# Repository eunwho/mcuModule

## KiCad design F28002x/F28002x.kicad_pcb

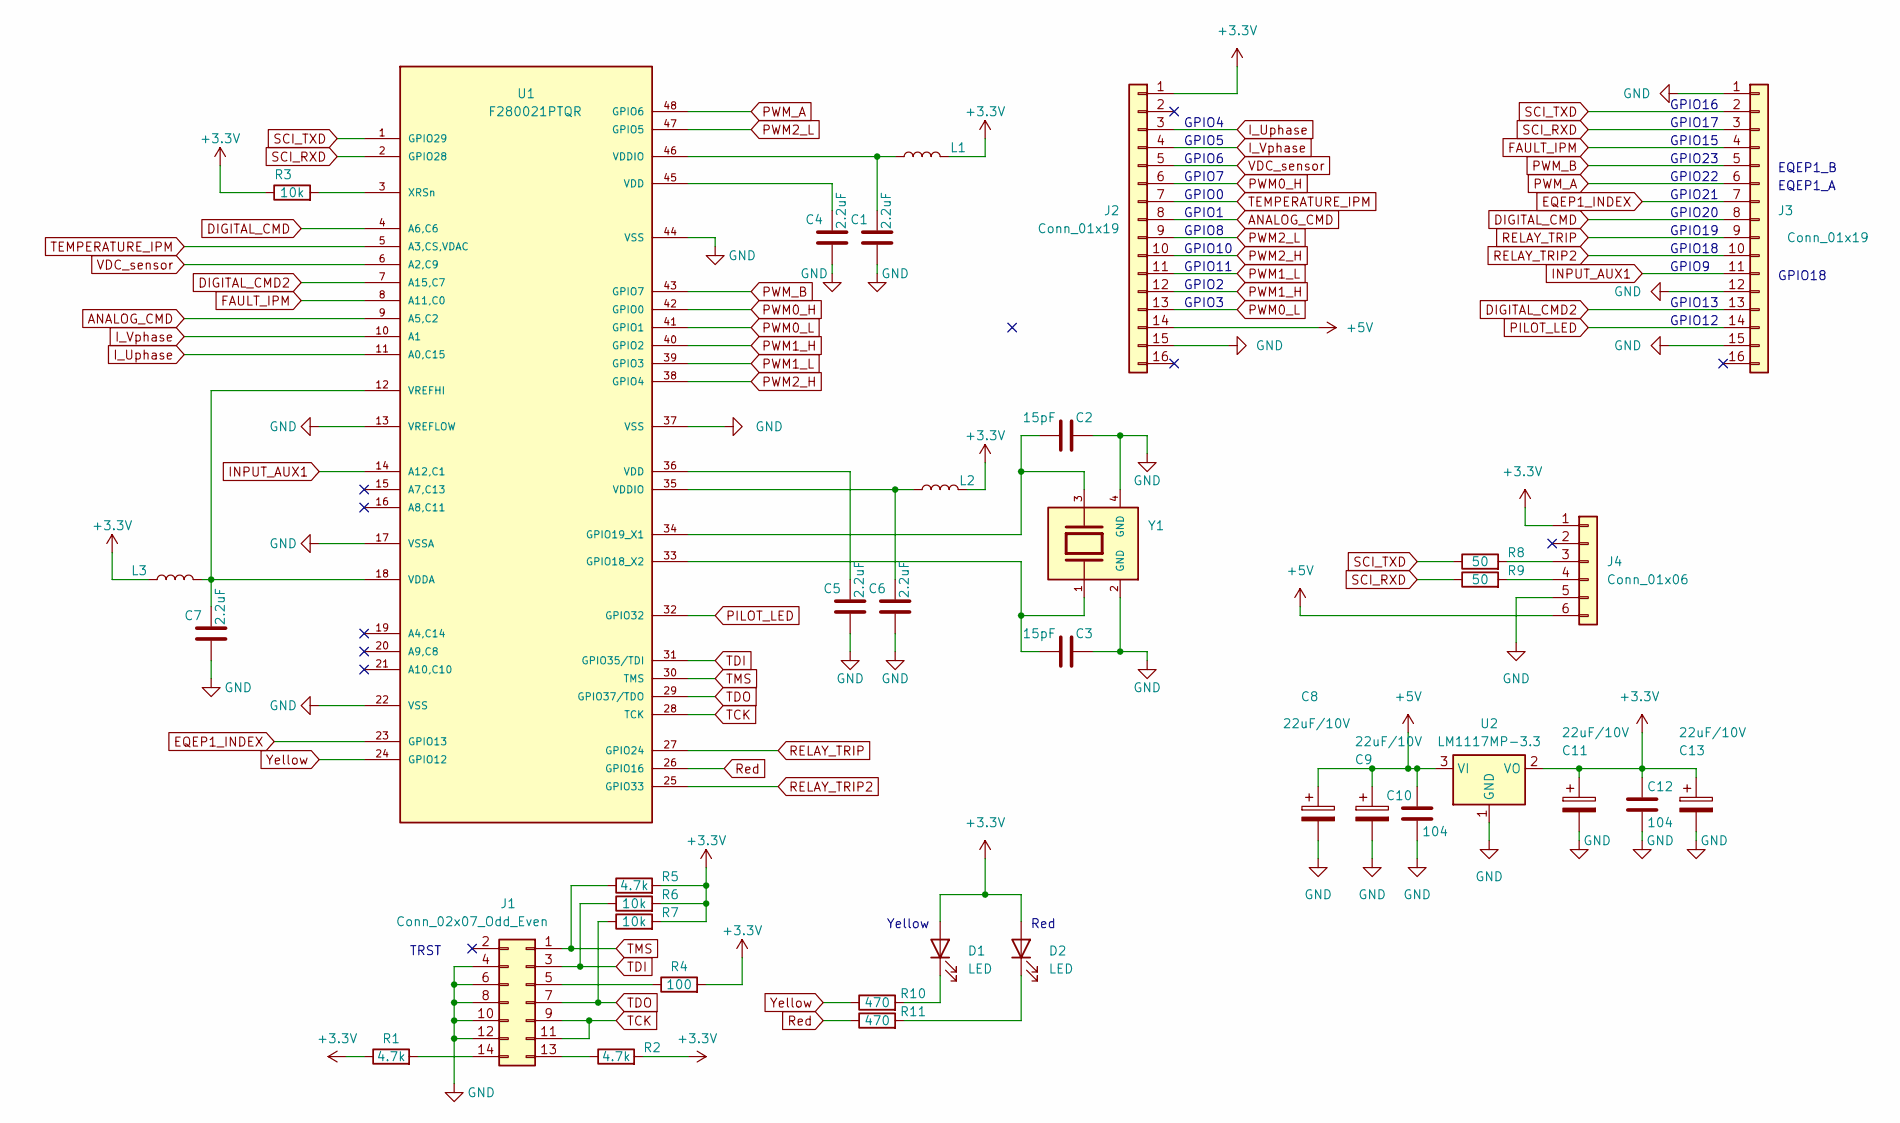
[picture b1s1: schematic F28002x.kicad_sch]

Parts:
C1, C4, C5, C6, C7: 2.2uF; C_0805_2012Metric
C2, C3: 15pF; C_0805_2012Metric
C8, C9, C11, C13: 22uF/10V; C_1210_3225Metric_Pad1.33x2.70mm_HandSolder
C10, C12: 104; C_0805_2012Metric
D1, D2: LED; LED_0805_2012Metric_Pad1.15x1.40mm_HandSolder
J1: Conn_02x07_Odd_Even; PinHeader_2x07_P2.54mm_Vertical
J2, J3: Conn_01x19; PinHeader_1x16_P2.54mm_Vertical
J4: Conn_01x06; PinHeader_1x06_P2.54mm_Vertical
L1, L2, L3: 2A/45mohm/220ohm@100Mhz; L_0805_2012Metric_Pad1.15x1.40mm_HandSolder; Part # BLM21PG221SN1D
R1, R2, R5: 4.7k; R_0805_2012Metric_Pad1.20x1.40mm_HandSolder
R3, R6, R7: 10k; R_0805_2012Metric_Pad1.20x1.40mm_HandSolder
R4: 100; R_0805_2012Metric_Pad1.20x1.40mm_HandSolder
R8, R9: 50; R_0805_2012Metric_Pad1.20x1.40mm_HandSolder
R10, R11: 470; R_0805_2012Metric_Pad1.20x1.40mm_HandSolder
U1: F280021PTQR; LQFP-48_7x7mm_P0.5mm; PARTREV J
U2: LM1117MP-3.3; SOT-223-3_TabPin2
Y1: ABM3B-20.000MHZ-B2-T; XTAL_ABM3B-20.000MHZ-B2-T; PARTREV 08.25.15

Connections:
+3.3V: C11.1, C12.2, C13.1, D1.2 (A), D2.2 (A), J2.1, J4.1, L1.1, L2.1, L3.1, R1.1, R2.2, R3.1, R4.2, R5.2, R6.2, R7.2, U2.2 (VO)
+5V: C8.1, C9.1, C10.2, J2.14, J4.6, U2.3 (VI)
ANALOG_CMD: J2.8, U1.9 (A5,C2)
DIGITAL_CMD: J3.8, U1.4 (A6,C6)
DIGITAL_CMD2: J3.13, U1.7 (A15,C7)
EQEP1_INDEX: J3.7, U1.23 (GPIO13)
FAULT_IPM: J3.4, U1.8 (A11,C0)
GND: C1.1, C2.1, C3.1, C4.1, C5.1, C6.1, C7.1, C8.2, C9.2, C10.1, C11.2, C12.1, C13.2, J1.4, J1.6, J1.8, J1.10, J1.12, J2.15, J3.1, J3.12, J3.15, J4.5, U1.13 (VREFLOW), U1.17 (VSSA), U1.22 (VSS), U1.37 (VSS), U1.44 (VSS), U2.1 (GND), Y1.2 (GND), Y1.4 (GND)
INPUT_AUX1: J3.11, U1.14 (A12,C1)
I_Uphase: J2.3, U1.11 (A0,C15)
I_Vphase: J2.4, U1.10 (A1)
unnamed: C1.2, L1.2, U1.46 (VDDIO)
unnamed: C4.2, U1.45 (VDD)
unnamed: C5.2, U1.36 (VDD)
unnamed: C6.2, L2.2, U1.35 (VDDIO)
unnamed: D1.1 (K), R10.2
unnamed: D2.1 (K), R11.2
unnamed: J1.5, R4.1
unnamed: J1.13, R2.1
unnamed: J1.14, R1.2
unnamed: J4.3, R8.2
unnamed: J4.4, R9.2
unnamed: C3.2, U1.33 (GPIO18_X2), Y1.1
unnamed: C2.2, U1.34 (GPIO19_X1), Y1.3
unnamed: C7.2, L3.2, U1.12 (VREFHI), U1.18 (VDDA)
unnamed: R3.2, U1.3 (XRSn)
PILOT_LED: J3.14, U1.32 (GPIO32)
PWM0_H: J2.6, U1.42 (GPIO0)
PWM0_L: J2.13, U1.41 (GPIO1)
PWM1_H: J2.12, U1.40 (GPIO2)
PWM1_L: J2.11, U1.39 (GPIO3)
PWM2_H: J2.10, U1.38 (GPIO4)
PWM2_L: J2.9, U1.47 (GPIO5)
PWM_A: J3.6, U1.48 (GPIO6)
PWM_B: J3.5, U1.43 (GPIO7)
RELAY_TRIP: J3.9, U1.27 (GPIO24)
RELAY_TRIP2: J3.10, U1.25 (GPIO33)
Red: R11.1, U1.26 (GPIO16)
SCI_RXD: J3.3, R9.1, U1.2 (GPIO28)
SCI_TXD: J3.2, R8.1, U1.1 (GPIO29)
TCK: J1.9, J1.11, U1.28 (TCK)
TDI: J1.3, R6.1, U1.31 (GPIO35/TDI)
TDO: J1.7, R7.1, U1.29 (GPIO37/TDO)
TEMPERATURE_IPM: J2.7, U1.5 (A3,CS,VDAC)
TMS: J1.1, R5.1, U1.30 (TMS)
VDC_sensor: J2.5, U1.6 (A2,C9)
Yellow: R10.1, U1.24 (GPIO12)

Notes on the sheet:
GPIO13
GPIO6
GPIO11
GPIO7
GPIO22
GPIO16
TRST
Red
GPIO15
GPIO8
GPIO18
GPIO4
GPIO1
GPIO2
Yellow
GPIO5
GPIO21
GPIO17
GPIO19
GPIO10
GPIO3
EQEP1_A
GPIO0
GPIO9
GPIO12
EQEP1_B
GPIO23
GPIO20

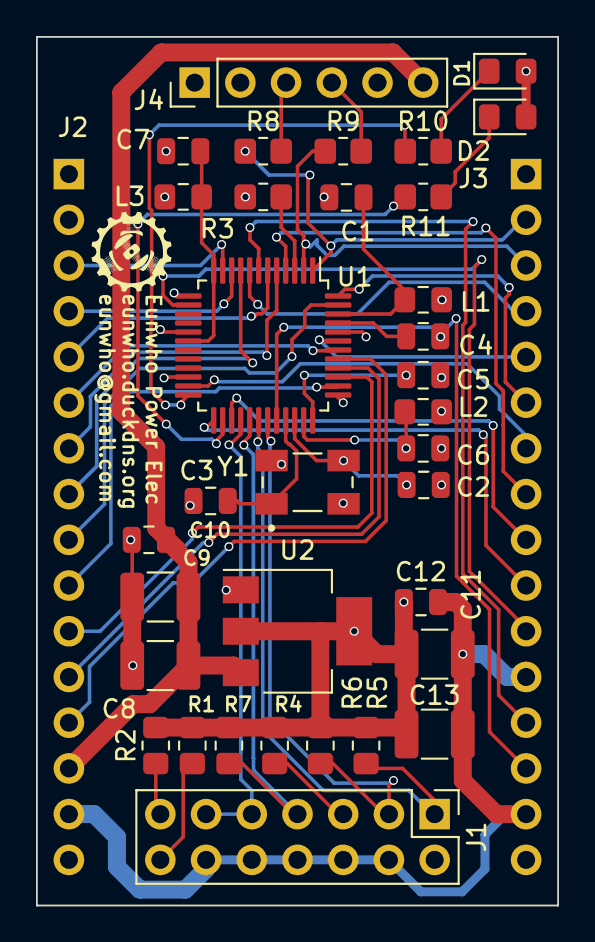
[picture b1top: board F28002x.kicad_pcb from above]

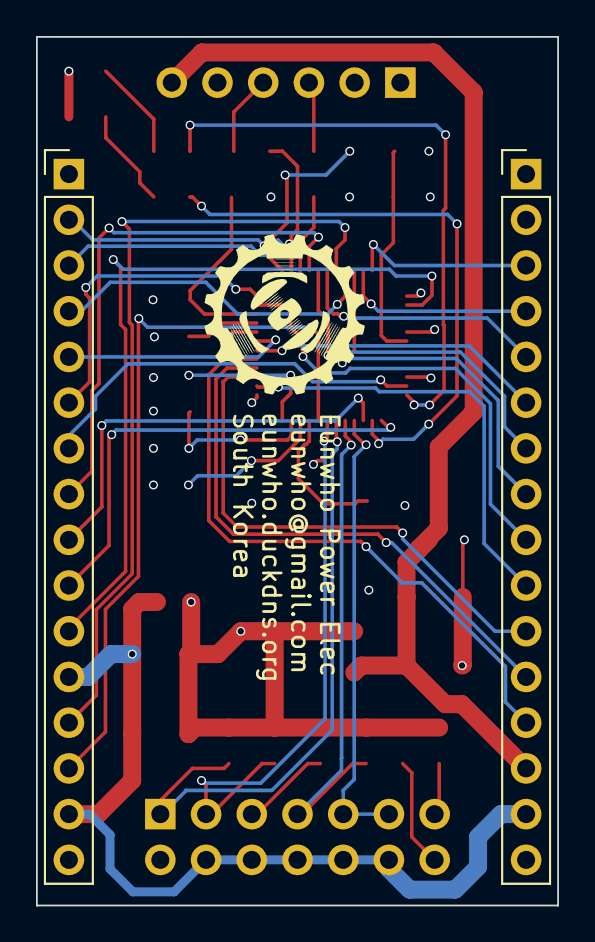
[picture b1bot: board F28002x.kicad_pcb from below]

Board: 4 copper layers, 29.0 x 48.3 mm, 36 parts (2 on the bottom side), 47 nets.

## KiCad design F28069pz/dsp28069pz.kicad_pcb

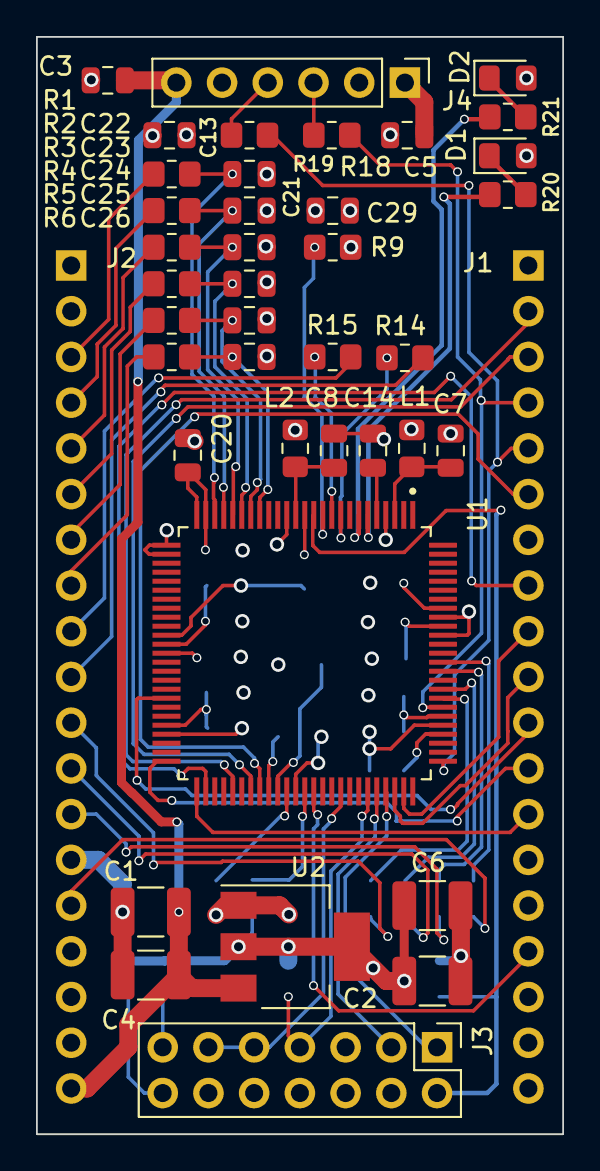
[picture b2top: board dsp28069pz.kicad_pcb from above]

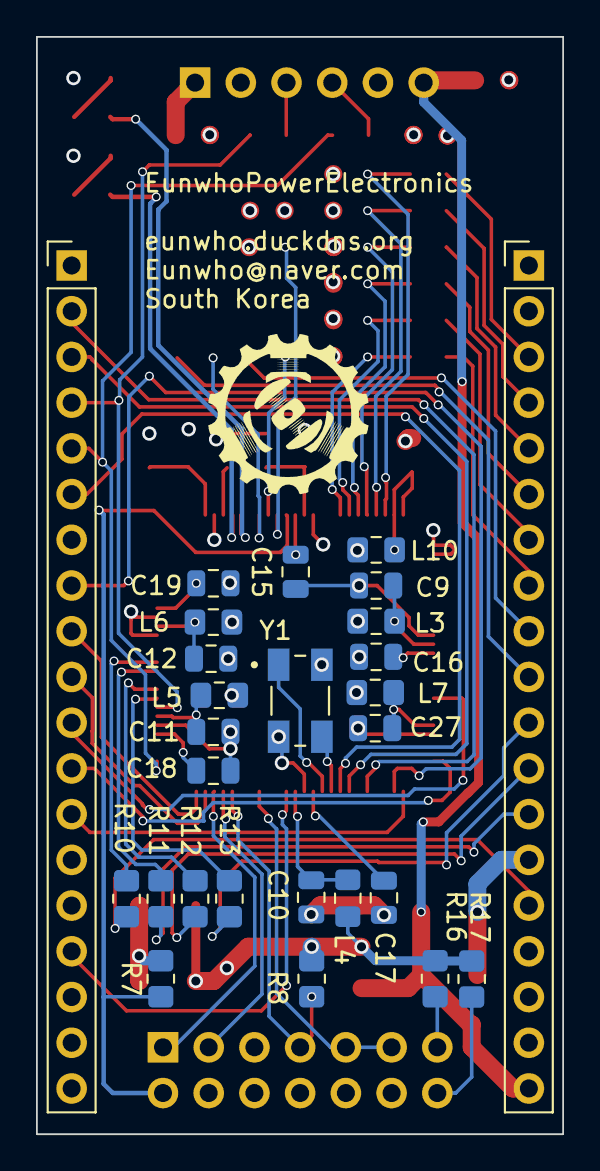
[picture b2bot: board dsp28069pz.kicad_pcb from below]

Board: 4 copper layers, 29.2 x 61.0 mm, 66 parts (27 on the bottom side), 69 nets.

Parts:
C1, C2, C4, C6: 22uF/10V; C_1210_3225Metric_Pad1.33x2.70mm_HandSolder
C3, C5: 104; C_0805_2012Metric
C7, C8, C9, C10, C11, C12, C13, C14, C15, C16, C17, C18, C19, C20, C21, C22, C23, C24, C25, C26, C27, C29: 2.2uF; C_0805_2012Metric
D1, D2: LED; LED_0805_2012Metric_Pad1.15x1.40mm_HandSolder
J1, J2: Conn_01x19; PinHeader_1x19_P2.54mm_Vertical
J3: Conn_02x07_Odd_Even; PinHeader_2x07_P2.54mm_Vertical
J4: Conn_01x06; PinHeader_1x06_P2.54mm_Vertical
L1, L2, L3, L4, L5, L6, L7, L10: 2A/45mohm/220ohm@100Mhz; L_0805_2012Metric_Pad1.15x1.40mm_HandSolder
R1, R2, R3, R4, R5, R6, R10, R11, R12, R13, R14, R15, R18, R19: 50; R_0805_2012Metric_Pad1.20x1.40mm_HandSolder
R7, R8: 2.2k; R_0805_2012Metric_Pad1.20x1.40mm_HandSolder
R9: 10k; R_0805_2012Metric_Pad1.20x1.40mm_HandSolder
R16, R17, R20, R21: 470; R_0805_2012Metric_Pad1.20x1.40mm_HandSolder
U1: TMS320F28069PZT; QFP50P1600X1600X160-100N
U2: LM1117MP-3.3; SOT-223-3_TabPin2
Y1: ABM3B-20.000MHZ-B2-T; XTAL_ABM3B-20.000MHZ-B2-T

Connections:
+3.3V: C2.1, C5.2, C6.1, C13.2, C29.2, D1.2 (A), D2.2 (A), J2.1, J3.5, J4.1, L1.1, L2.1, L3.1, L4.1, L5.1, L6.1, L7.1, L10.1, R8.2, R9.1, R16.2, R17.1, U2.2 (VO)
+5V: C1.1, C3.2, C4.1, J2.19, J4.6, U2.3 (VI)
ANALOG_CMD: J2.6, R4.1
ANALOG_CMD2: J2.8, R6.1
DIGITAL_CMD: J1.8, U1.52 (GPIO17)
DIGITAL_CMD2: J1.13, U1.51 (GPIO18/XCLKOUT)
FAULT_IPM: J1.2, U1.55 (GPIO16)
GND: C1.2, C2.2, C3.1, C4.2, C5.1, C6.2, C7.1, C8.1, C9.1, C10.1, C11.1, C12.1, C13.1, C14.1, C15.1, C16.1, C17.1, C18.1, C19.1, C20.1, C21.1, C22.1, C23.1, C24.1, C25.1, C26.1, C27.1, C29.1, J1.1, J1.7, J2.14, J3.4, J3.6, J3.8, J3.10, J3.12, J4.5, R7.2, U1.4 (VSS), U1.15 (VSS), U1.26 (VSSA), U1.27 (VREFLO), U1.36 (VSS), U1.47 (VSS), U1.62 (VSS), U1.80 (VSS), U1.90 (~VREGENZ), U1.92 (VSS), U2.1 (GND), Y1.2 (GND), Y1.4 (GND)
I_Uphase: J2.3, R1.1
I_Vphase: J2.4, R2.1
unnamed: C7.2, L1.2, U1.3 (VDD)
unnamed: C8.2, L2.2, U1.14 (VDD)
unnamed: C9.2, L3.2, U1.37 (VDD)
unnamed: C10.2, L4.2, U1.63 (VDD)
unnamed: C11.2, L5.2, U1.81 (VDD)
unnamed: C12.2, L6.2, U1.91 (VDD)
unnamed: C14.2, U1.5 (VDDIO)
unnamed: C15.2, U1.13 (VDDIO)
unnamed: C16.2, U1.38 (VDDIO)
unnamed: C17.2, U1.61 (VDDIO)
unnamed: C18.2, U1.79 (VDDIO)
unnamed: C19.2, U1.93 (VDDIO)
unnamed: D1.1 (K), R20.2
unnamed: D2.1 (K), R21.2
unnamed: J3.13, R16.1
unnamed: J3.14, R17.2
unnamed: J4.3, R18.2
unnamed: J4.4, R19.2
unnamed: C21.2, R1.2, U1.23 (ADCINA0)
unnamed: C22.2, R2.2, U1.22 (ADCINA1)
unnamed: C23.2, R3.2, U1.21 (ADCINA2)
unnamed: C24.2, R4.2, U1.20 (ADCINA3)
unnamed: C25.2, R5.2, U1.19 (ADCINA4)
unnamed: C26.2, R6.2, U1.18 (ADCINA5)
unnamed: R10.2, U1.87 (GPIO0)
unnamed: R11.2, U1.86 (GPIO1)
unnamed: R12.2, U1.84 (GPIO2)
unnamed: R13.2, U1.83 (GPIO3)
unnamed: R14.2, U1.9 (GPIO4)
unnamed: R15.2, U1.10 (GPIO5)
unnamed: R20.1, U1.6 (GPIO20)
unnamed: R21.1, U1.7 (GPIO21)
unnamed: C27.2, L7.2, U1.46 (VDD3VFL)
unnamed: C20.2, L10.2, U1.24 (VREFHI), U1.25 (VDDA)
unnamed: U1.60 (X1), Y1.1
unnamed: U1.59 (X2), Y1.3
unnamed: R9.2, U1.11 (~XRS)
PILOT_LED: J1.16, U1.64 (GPIO19/XCLKIN)
PWM0_H: J2.15, R10.1
PWM0_L: J2.13, R11.1
PWM1_H: J2.12, R12.1
PWM1_L: J2.11, R13.1
PWM2_H: J2.10, R14.1
PWM2_L: J2.9, R15.1
PWM_A: J1.6, U1.58 (GPIO6)
PWM_B: J1.3, U1.57 (GPIO7)
RELAY_TRIP: J1.9, U1.74 (GPIO10)
RELAY_TRIP2: J1.10, U1.73 (GPIO11)
SCI_RXD: J1.12, U1.50 (GPIO28)
SCI_RXD0: J1.5, R19.1, U1.76 (GPIO41)
SCI_TXD: J1.11, U1.43 (GPIO29)
SCI_TXD0: J1.4, R18.1, U1.82 (GPIO40)
TCK: J3.9, J3.11, U1.67 (GPIO38/XCLKIN/TCK)
TDI: J3.3, U1.71 (GPIO35/TDI)
TDO: J3.7, R8.1, U1.70 (GPIO37/TDO)
TEMPERATURE_IPM: J2.7, R5.1
TMS: J3.1, U1.72 (GPIO36/TMS)
VDC_sensor: J2.5, R3.1
\TRST: J3.2, R7.1, U1.12 (~TRST)
